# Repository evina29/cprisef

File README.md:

# CPRISEF: Hands Free CPR Compression Rig with AI Guidance

CPRISEF is a hands free CPR compression rig with AI guidance. A motor and a gearbox push a pad up and down at a steady 120 compressions a minute, a load cell feels every push, and a buzzer tells you when the pace slips.

With a scotch yoke that turns a spinning motor into a straight 50 mm push, and a Raspberry Pi Pico that watches the force, CPRISEF is a machine that never gets tired.

When someone collapses, good chest compressions have to start right away and stay at a steady pace. But rescuers get tired in about two minutes, their depth and rhythm drift, and most people doing CPR have never practiced. I wanted to see if a machine could hold the pace so the people around can call for help and focus on the rescue. Then I wanted to add an AI layer on top that tells the rescuer what to do next. I am doing this because it felt like a hardware problem that actually matters.

I am designing CPRISEF for ISEF and for Hack Club's Fallen. My build log is in [JOURNAL.md](JOURNAL.md).

CPRISEF is a science fair project and not a medical device. It only ever gets tested on a manikin or a force sensor, never on a person.

## Features

* 150 W DC motor with a two stage 25 to 1 spur gear reduction
* Scotch yoke that gives a straight 50 mm stroke at 120 compressions a minute
* About 500 N of peak force
* Load cell and HX711 amplifier that measure every compression
* Raspberry Pi Pico on a custom 70 by 70 mm interface board
* Buzzer and status LED that warn when the rate leaves the 100 to 120 per minute window
* Emergency stop input
* UART link to a Raspberry Pi 5 that will run the AI guidance
* Gears that I design and print myself

## Frame and mechanism

The whole rig is written in Python with CadQuery in cprisef.py, so I can change a number and rebuild everything. The frame is wood. The motor drives a two stage gearbox, the gearbox turns a crank, and the crank moves a scotch yoke that pushes the pad.

To rebuild the CAD:

    pip install -r requirements.txt
    python cprisef.py cprisef_rig.step
    python export_parts.py step

The first command writes the full assembly as one STEP file that opens in Onshape or any other CAD tool. The second writes one STEP file for every part. Both are already in the repo, in cprisef_rig.step and the step folder.

| Item | Value |
|---|---|
| Motor | 150 W DC, 3000 rpm, 12 V version |
| Gearbox | Two stage spur gears, 25 to 1 total |
| Gear module | 1.5, with 16 tooth and 80 tooth gears |
| Output speed | 120 compressions per minute |
| Mechanism | Scotch yoke, 25 mm crank radius |
| Stroke | 50 mm |
| Peak force | About 500 N |

## Gears

The gears are the one part I make myself. I design them in cprisef.py and print them in PETG. The rig peaks at about 500 N, so I will check how the printed teeth hold up before I trust them.

## PCB

The interface board connects the Pico to the HX711 load cell amplifier, the emergency stop input, a buzzer, a status LED and the UART link to the Pi. It is a 70 by 70 mm board with two layers, a ground pour on the bottom and four mounting holes. It carries no motor current, because the motor runs from a speed controller I buy ready made.

I generate the KiCad files and gerbers with pcb/make_pcb.py, then opened them in KiCad 7. The design rule check finds no errors once the ground zone is filled, which you do by pressing B in the PCB editor. KiCad only warns that the footprints are embedded instead of coming from a library. I have not ordered boards yet.

The KiCad project is in pcb/kicad and the fabrication files, including gerbers.zip, are in pcb/gerbers.

## Schematic and wiring

The schematic is in pcb/kicad/cprisef.kicad_sch.

## Firmware

The firmware runs on the Pico in MicroPython. It reads the load cell, finds each compression as a force peak, works out the rate, sounds the buzzer if the rate is off or the emergency stop is pressed, and sends the rate to the Raspberry Pi once a second. It is written for this board and has not run on real hardware yet.

Libraries used:

None. It only uses MicroPython's built in modules, json, time and machine.

Instructions:

1. Flash MicroPython onto the Pico. Hold the BOOTSEL button while you plug it in, then copy the .uf2 file over.
2. Open the Pico in Thonny.
3. Save firmware/main.py on the Pico as main.py.
4. Set COUNTS_PER_NEWTON and PEAK_FORCE using a known weight, since they need calibrating on the real rig.

## Parts

Everything is from Amazon, except the gears, which I print from filament. bom.csv has a link, a price estimate and an owned note for every item. The estimated total is about $685 before tax and shipping, and I own none of the parts yet. The camera for the AI stage is not in the list, because that stage comes later and I will get it myself.

## Files in this repo

| Path | What it is |
|---|---|
| cprisef.py | CAD source for the whole rig |
| cprisef_rig.step | The full assembly as one STEP file |
| step/ | One STEP file for each of the 14 parts |
| export_parts.py | Writes the STEP file for each part |
| pcb/kicad/ | KiCad project, schematic and board |
| pcb/gerbers/ | Gerbers, drill files and gerbers.zip |
| pcb/make_pcb.py | Script that generates the KiCad files and gerbers |
| firmware/main.py | MicroPython firmware for the interface board |
| bom.csv | Bill of materials |
| JOURNAL.md | Build journal |
| docs/ | The pictures used in this README |

## Safety and ethics

No human participants are involved. The rig is only tested on a manikin or a force sensor, never on a person. The motor circuit has a fuse and an emergency stop, and the emergency stop has to be rated for the motor current of about 12.5 A. Wiring the power cord to the supply involves mains voltage, so only someone who can do it safely should do it.

CPRISEF must never be used on a real patient. It follows the ISEF rules on safety, ethics, academic integrity and generative AI.

## Credits

The design that inspired this project is credited in my project paperwork. The CAD comes from cprisef.py with CadQuery, and the KiCad files and gerbers come from pcb/make_pcb.py.

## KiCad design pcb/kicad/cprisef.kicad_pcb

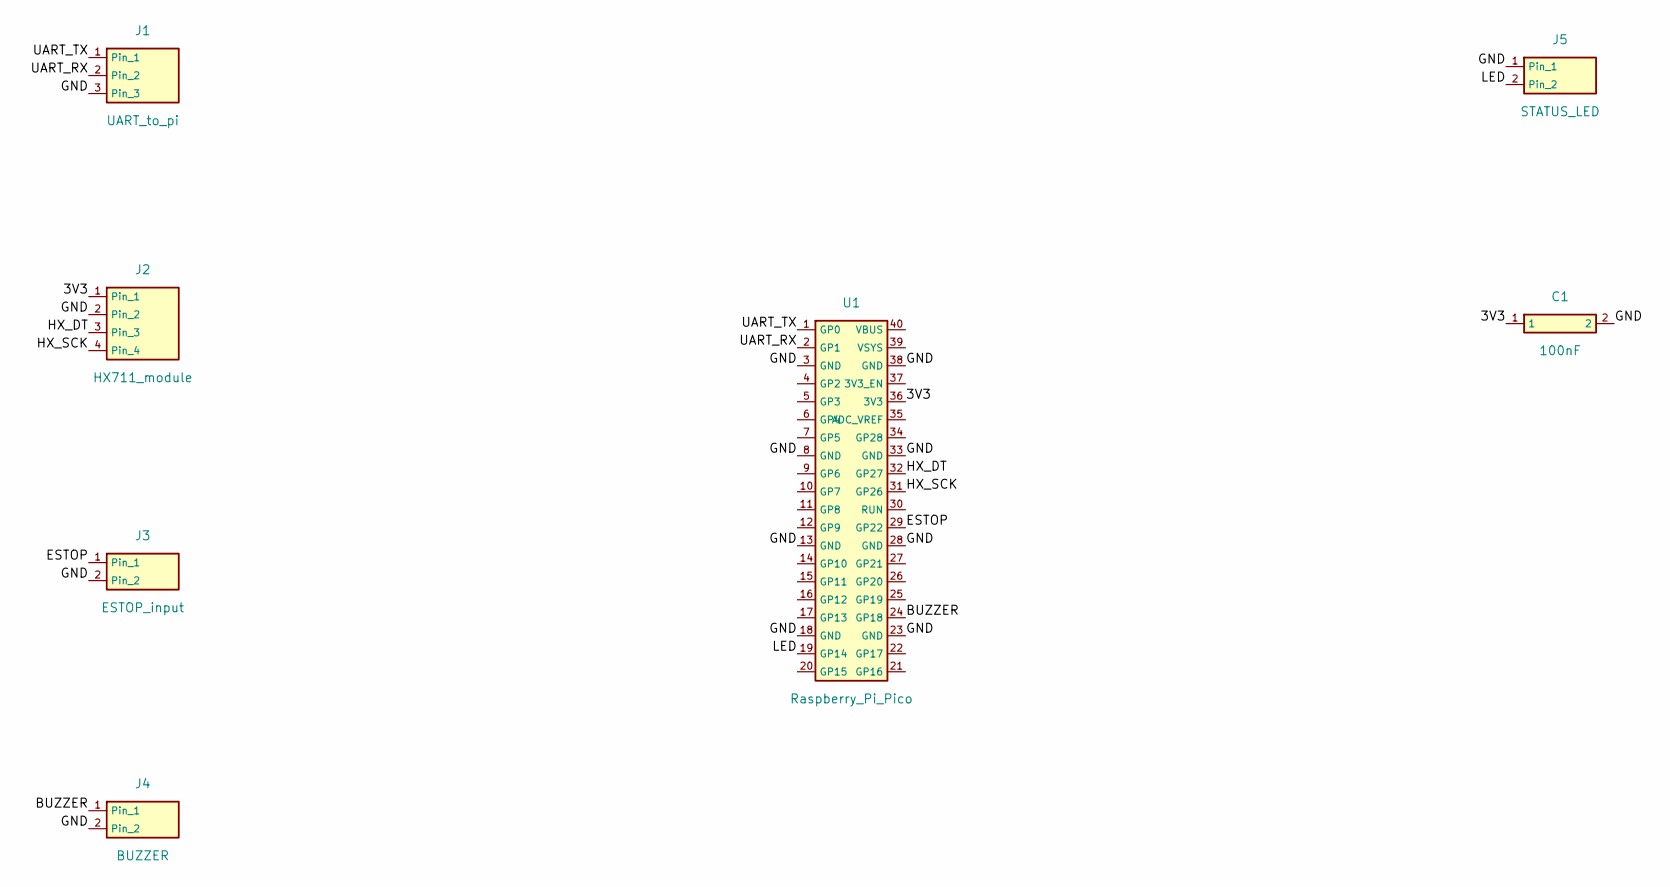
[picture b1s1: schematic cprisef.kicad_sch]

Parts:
C1: 100nF; C_Disc_P2.54mm
J1: UART_to_pi; Header_1x03_P2.54mm
J2: HX711_module; Header_1x04_P2.54mm
J3: ESTOP_input; Header_1x02_P2.54mm
J4: BUZZER; Header_1x02_P2.54mm
J5: STATUS_LED; Header_1x02_P2.54mm
U1: Raspberry_Pi_Pico; RPi_Pico_THT

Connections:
3V3: C1.1, J2.1, U1.36 (3V3)
BUZZER: J4.1, U1.24 (GP18)
ESTOP: J3.1, U1.29 (GP22)
GND: C1.2, J1.3, J2.2, J3.2, J4.2, J5.1, U1.3 (GND), U1.8 (GND), U1.13 (GND), U1.18 (GND), U1.23 (GND), U1.28 (GND), U1.33 (GND), U1.38 (GND)
HX_DT: J2.3, U1.32 (GP27)
HX_SCK: J2.4, U1.31 (GP26)
LED: J5.2, U1.19 (GP14)
UART_RX: J1.2, U1.2 (GP1)
UART_TX: J1.1, U1.1 (GP0)

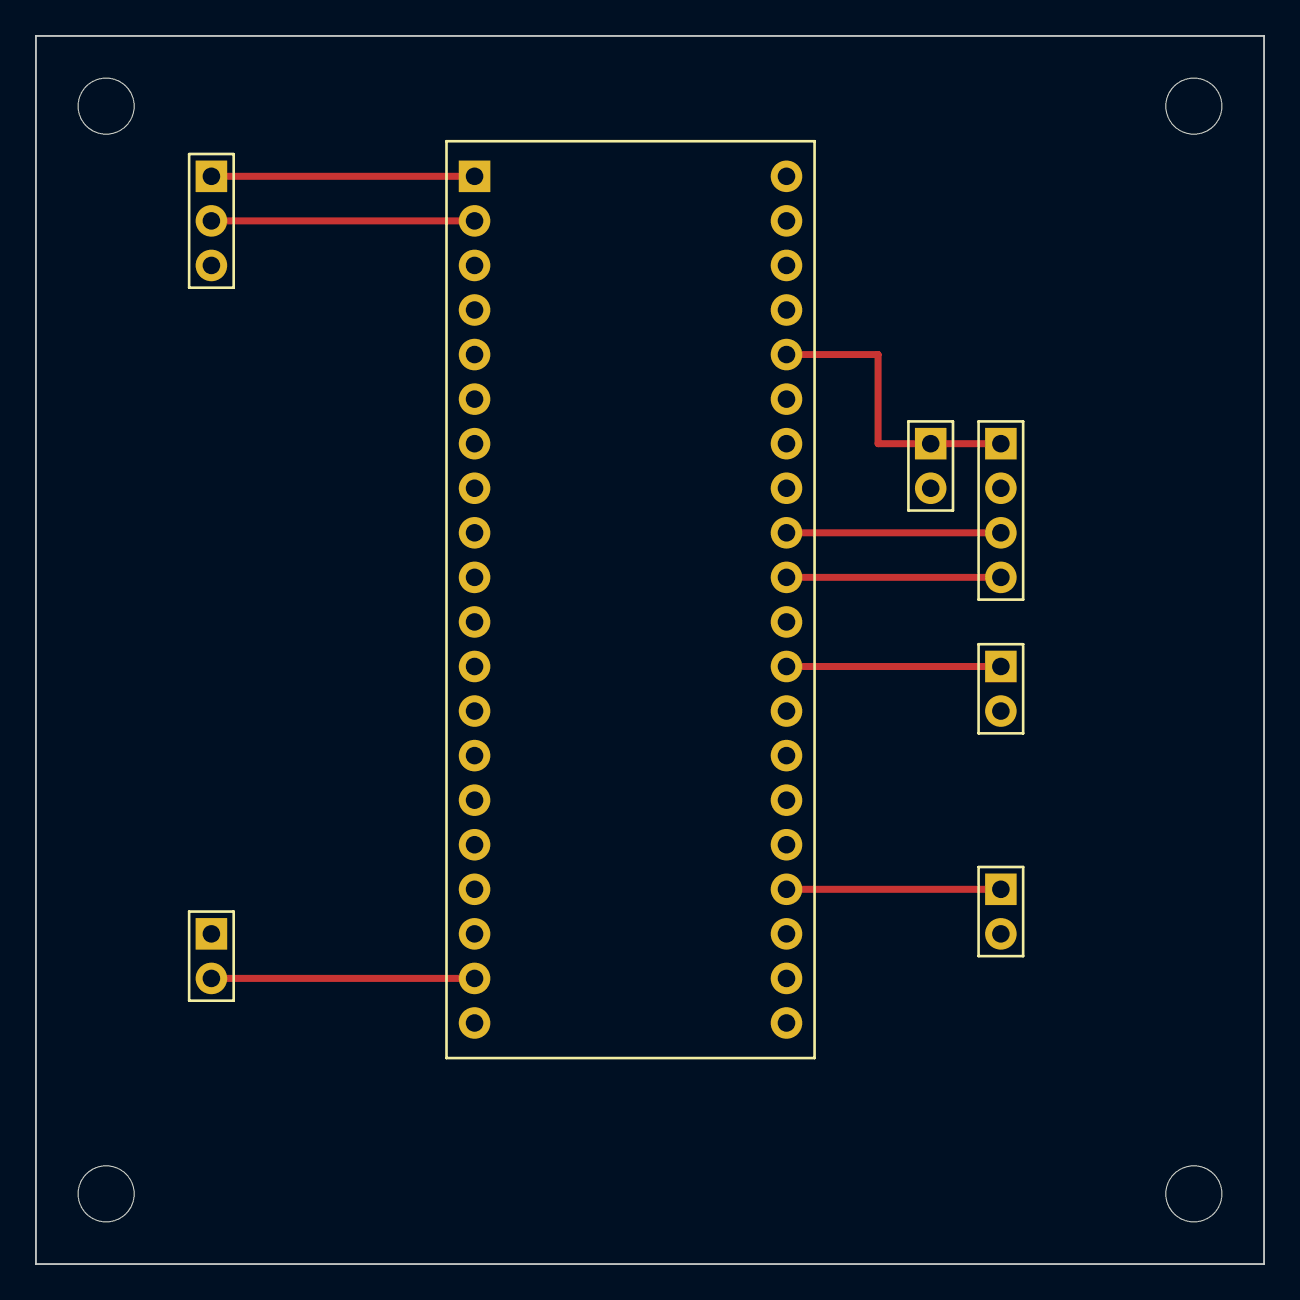
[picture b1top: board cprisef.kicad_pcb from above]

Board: 2 copper layers, 70.0 x 70.0 mm, 11 parts (0 on the bottom side), 9 nets.

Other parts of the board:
H1, H2, H3, H4: MountingHole; MountingHole_3.2mm
